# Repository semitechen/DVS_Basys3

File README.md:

# 🎧 Digital Vinyl System (DVS) on FPGA Basys 3

[-brightgreen.svg)](#fpga-resource-utilization--timing-closure)

An autonomous, ultra-low-latency **Digital Vinyl System (DVS)** and lossless SD audio player implemented entirely in hardware on dual **Digilent Basys 3 (Xilinx Artix-7)** FPGA boards and custom analog front-end / R-2R DAC PCB shields.

---

## 🎬 Video Demonstration

Click the preview below to watch the complete hardware setup in action, demonstrating real-time scratch, pitch-shifting, backward playback, cueing, track selection, and autonomous QSPI Flash boot:

---

## 📸 Hardware Gallery

<p align="center">
  
  <br>
  <em>Figure 1: Complete real-time test bench with analog turntable (Serato 1 kHz timecode vinyl), custom pre-amp/filter shield, Board A (Streamer), Board B (DAC Receiver), and audio output.</em>
</p>

<p align="center">

  <br>
  <em>Figure 2: Custom AC-coupling pre-amplifier, active Sallen-Key low-pass filter, and 8-bit R-2R resistor ladder DAC PCB shield designed for Basys 3 Pmod headers.</em>
</p>

---

## 📌 Project Overview & Motivation

### Why Hardware DVS?
In modern DJing, **Digital Vinyl Systems (DVS)** bridge tactile analog turntables with digital music libraries. However, commercial DVS setups require:
1. A laptop running resource-intensive software (Serato, Traktor, Rekordbox).
2. Dedicated USB soundcards.
3. Operating system audio buffers (introducing $5\text{--}20\text{ ms}$ of latency, audio dropouts, and CPU jitter).

### The FPGA Solution
This project eliminates the computer entirely. By executing all timecode signal processing, quadrant phase decoding, flash memory DMA, rate modulation, and audio reconstruction **directly in FPGA silicon at 100 MHz**:
* **Sub-Microsecond Latency:** From vinyl needle motion to DAC audio output in $< 5.0\,\mu\text{s}$.
* **Zero Software Dependency:** Autonomous non-volatile boot from onboard QSPI Flash.
* **Lossless Playback:** Real-time variable-rate streaming of uncompressed 8-bit PCM audio ($44.1\text{ kHz}$) directly from FAT-less micro-SD sectors.
* **Audiophile Reconstruction:** 16x oversampling engine with a 1st-order Noise Shaper ($1 - z^{-1}$) and Triangular Probability Density Function (TPDF) dither, dramatically suppressing resistor ladder quantization noise.

---

## 🏛️ System Architecture

The project employs a distributed **Dual-Board FPGA Architecture** linked by a dedicated **2,000,000 baud (2 Mbps)** UART audio bus:

```
+---------------------------------------------------------------------------------------------------------+
|                                    BOARD A: TIME-CODE STREAMER & SD PLAYER                              |
|                                                                                                         |
|  [Turntable] ---> [Custom PCB Pre-amp] ---> [XADC (vauxp6/14)]                                          |
|                                                     |                                                   |
|                                            [xadc_interface]                                             |
|                                                     | x2t (12-bit L/R @ 100 kHz)                        |
|                                                     v                                                   |
|                                          [timecode_pos_tracker] <---> [led_pos_display] (16 LEDs)        |
|                                                     |                                                   |
|                                                     | t2p (Q4.12 Speed, Direction, Squelch)             |
|                                                     v                                                   |
|  [Micro-SD] <--- [sd_card_controller] <--- [sd_bram_bridge]                                            |
|                       (16.67 MHz SPI)               | b2f (512-byte Sector Writes)                      |
|                                                     v                                                   |
|                                              [audio_fifo] (1024-byte Dual-Port BRAM)                    |
|                                                     |                                                   |
|                                                     | f2p (Read FIFO Sample)                            |
|                                                     v                                                   |
|                                         [variable_speed_player] (NCO Phase Acc)                         |
|                                                     |                                                   |
|                                                     | p2u (8-bit PCM Sample Valid)                      |
|                                                     v                                                   |
|                                                [uart_tx] (2 Mbps Transmitter)                           |
+-----------------------------------------------------|---------------------------------------------------+
                                                      | Pmod JC1 (K17) + GND
                                                      | 2.0 Mbps Audio Stream
+-----------------------------------------------------v---------------------------------------------------+
|                                      BOARD B: DAC & VISUALIZATION ENGINE                                |
|                                                                                                         |
|                                                [uart_rx] (2 Mbps Receiver)                              |
|                                                     |                                                   |
|                                                     | u2d (8-bit PCM Sample Valid)                      |
|                                                     v                                                   |
|       +---------------------------------------------+---------------------------------------------+     |
|       |                                                                                           |     |
|       v                                                                                           v     |
|  [audio_watchdog] (200 ms Timeout)                                                           [vu_meter] |
|       |                                                                                           |     |
|       v                                                                                           v     |
|  [r2r_dac] (16x Oversampling, 1st-Order Noise Shaping, TPDF Dither)                         [LED 11:0]  |
|       |                                                                                   (12-LED VU)   |
|       v (dac[7:0])                                                                                      |
|  [8-bit R-2R Resistor Ladder] ---> [Active Sallen-Key Low-Pass Filter] ---> [Audio Output / Amp]        |
+---------------------------------------------------------------------------------------------------------+
```

---

## 🔬 Deep-Dive: Core DSP & Hardware Modules

### 1. Dual-Channel XADC & Dynamic DC Estimator (`xadc_interface.sv`)
* Samples differential analog timecode inputs from Pmod JXADC (`vauxp6/vauxn6` for Left, `vauxp14/vauxn14` for Right).
* A 32-bit fixed-point 1st-order IIR low-pass filter dynamically tracks and subtracts the DC bias offset ($\approx 0.6\text{ V}$ operating point), ensuring pure zero-centered AC timecode signals.

### 2. High-Sensitivity Squelch & 4x Quadrature Decoder (`timecode_pos_tracker.sv`)
* **Hysteresis Schmitt-Triggers:** Dual digital Schmitt-triggers reject vinyl groove noise while tracking low-amplitude signals down to $16\text{ mV}$.
* **Envelope Squelch Gate:** Computes signal envelope with fast attack and exponential decay. If the needle is lifted ($< 20\text{ mV}$), the audio player is instantly muted.
* **4x Gray-Code State Machine:** Decodes state transitions $((0,0) \to (0,1) \to (1,1) \to (1,0))$, generating 4 step pulses per $1\text{ kHz}$ timecode cycle ($11.025$ audio samples per step).
* **Sequential Multi-Cycle Divider:** Measures clock cycles between pulses and executes an iterative 16-cycle restoring division ($102,400,000 / \Delta t$) to compute the exact speed factor in **Q4.12 fixed-point** ($16'\text{h}1000 = 1.0\times$) with zero combinational timing violations.

### 3. SPI SD Card Controller & BRAM Ring Buffer (`sd_card_controller.sv`, `sd_bram_bridge.sv`, `audio_fifo.sv`)
* High-speed SPI master operating at **16.67 MHz** (after 200 kHz CMD0/CMD8/ACMD41/CMD16 initialization).
* Issues single-block read commands (`CMD17`) to fetch uncompressed 512-byte PCM audio sectors into a 1024-byte dual-port Block RAM FIFO (`audio_fifo.sv`), maintaining an autonomous prefetch waterlevel.

### 4. Numerically Controlled Oscillator (NCO) Player (`variable_speed_player.sv`)
* A 32-bit phase accumulator driven by the formula:
  $$\Delta \text{Phase} = \frac{44100 \times 2^{32}}{100\,000\,000} \times \text{speed\_factor}$$
* Overflow pulses generate exact, cycle-accurate FIFO read requests, enabling continuous variable-speed pitch modulation from $0.01\times$ to $4.0\times$, forward and backward scratching.

### 5. 2 Mbps High-Speed Inter-Board UART (`uart_tx.sv`, `uart_rx.sv`)
* Transmits 8-bit audio frames across Pmod JC1 (`K17`) at **2,000,000 baud** ($50\text{ clock cycles per bit}$ at 100 MHz, $0.00\%\text{ baud error}$).
* Transmission time is only $5.0\,\mu\text{s}$ per byte, allowing real-time sample transmission with zero FIFO buffering on Board B.
* Includes a **200 ms watchdog** on Board B that smoothly returns the DAC to mid-scale silence ($128 / 1.65\text{ V}$) if the communication cable is unplugged.

### 6. 16x Noise-Shaped DAC Engine (`r2r_dac.sv`)
* **16x Oversampling:** Interpolates $44.1\text{ kHz}$ PCM to $705.6\text{ kHz}$.
* **1st-Order Noise Shaping:** Implements a closed-loop error-feedback filter ($H(z) = 1 - z^{-1}$) shifting quantization noise into the inaudible ultrasonic spectrum ($> 50\text{ kHz}$).
* **TPDF Dither:** Employs dual Galois Linear Feedback Shift Registers (LFSR) generating Triangular Probability Density Function dither to eliminate harmonic distortion and limit cycles.

---

## 📐 Custom PCB: Pre-Amplifier & R-2R DAC Shield

The project includes a custom 2-layer PCB shield designed in KiCad 8 that mounts directly onto the Basys 3 Pmod headers (`pcb/` directory):

<p align="center">
  
  <br>
  <em>Figure 3: KiCad Schematic showing dual-channel AC coupling, DC bias network, 2nd-order active Sallen-Key low-pass filter, and 8-bit R-2R resistor DAC ladder.</em>
</p>

<p align="center">
  
  <br>
  <em>Figure 4: KiCad 2-layer PCB layout with dedicated analog/digital ground separation and ultra-compact Pmod form-factor.</em>
</p>

---

## 🎛️ Hardware Setup & Pinout Guide

### Board A: Timecode Streamer (`top_board_a_streamer`)
| Function | Basys 3 Pin | Header / Pin Name | Description |
| :--- | :---: | :---: | :--- |
| **System Clock** | `W5` | `CLK` | 100.00 MHz onboard oscillator |
| **Global Reset** | `U18` | `BTNC` | Pushbutton active-high synchronous reset |
| **Track Next** | `T18` | `BTNU` | Advance to next audio track |
| **Track Prev** | `U17` | `BTND` | Return to previous audio track |
| **Mode Switch** | `V17` | `SW0` | `1` = DVS Vinyl Control, `0` = Standalone Auto-Play |
| **Timecode L+ / L-** | `J3` / `K3` | Pmod JXADC Pin 1 / 7 | Left channel differential input (`vauxp6/vauxn6`) |
| **Timecode R+ / R-** | `L3` / `M3` | Pmod JXADC Pin 2 / 8 | Right channel differential input (`vauxp14/vauxn14`) |
| **SD SPI CS** | `J1` | Pmod JA Pin 1 | Micro-SD Card Chip Select (active-low) |
| **SD SPI MISO** | `L2` | Pmod JA Pin 2 | Micro-SD Master-In Slave-Out (pull-up enabled) |
| **SD SPI MOSI** | `J2` | Pmod JA Pin 3 | Micro-SD Master-Out Slave-In |
| **SD SPI SCK** | `G2` | Pmod JA Pin 4 | Micro-SD SPI Clock (16.67 MHz) |
| **UART Audio TX** | `K17` | Pmod JC Pin 1 | 2 Mbps serial audio transmitter to Board B |
| **Ground (GND)** | `GND` | Pmod JC Pin 5/11 | Common ground reference line |
| **Platter LEDs** | `LED[12:0]` | Onboard LEDs | One-hot rotating vinyl position indicator |
| **Squelch LED** | `LED13` | Onboard LED | Needle presence indicator ($> 20\text{ mV}$) |
| **Direction LED**| `LED14` | Onboard LED | `1` = Forward, `0` = Reverse scratch |
| **Heartbeat LED**| `LED15` | Onboard LED | 100 MHz clock live blinker |

---

### Board B: DAC Output & VU-Meter (`top_board_b_dac`)
| Function | Basys 3 Pin | Header / Pin Name | Description |
| :--- | :---: | :---: | :--- |
| **System Clock** | `W5` | `CLK` | 100.00 MHz onboard oscillator |
| **Global Reset** | `U18` | `BTNC` | Reset watchdog and DAC state |
| **UART Audio RX** | `K17` | Pmod JC Pin 1 | 2 Mbps serial audio receiver from Board A |
| **Ground (GND)** | `GND` | Pmod JC Pin 5/11 | Common ground reference line |
| **DAC Bit 0..3** | `G3, H2, K2, H1` | Pmod JA Pins 10, 9, 8, 7 | R-2R ladder lower nibble (`dac[0..3]`) |
| **DAC Bit 4..7** | `M2, M1, N2, N1` | Pmod JXADC Pins 3, 9, 4, 10 | R-2R ladder upper nibble (`dac[4..7]`) |
| **VU-Meter LEDs** | `LED[11:0]` | Onboard LEDs | 12-LED dynamic audio level bargraph |
| **Watchdog LED** | `LED14` | Onboard LED | Audio stream activity monitor |
| **Heartbeat LED**| `LED15` | Onboard LED | 100 MHz clock live blinker |

---

## ⚡ Autonomous QSPI Flash Boot Setup

Both boards can run autonomously without a computer attached:

1. **Set Boot Jumpers:** On both Basys 3 boards, locate the **`JP1` (MODE)** jumper header and set the jumper block to **`QSPI`** (middle pin bridged to the top pin).
2. **Flash Bitstreams to SPI ROM:**
   ```bash
   # Flash Board A (Timecode Streamer)
   ./tools/program_fpga.sh -t board_a -f -s <SERIAL_BOARD_A>

   # Flash Board B (DAC Engine)
   ./tools/program_fpga.sh -t board_b -f -s <SERIAL_BOARD_B>
   ```
3. Connect Board A Pmod JC1 to Board B Pmod JC1, connect common GND, and power on both boards via any USB power supply.

---

## 📊 FPGA Resource Utilization & Timing Closure

Synthesized and implemented for **Xilinx Artix-7 XC7A35T-1CPG236C** in Vivado 2023.2:

| Resource | Available | Board A (Streamer) | Utilization A | Board B (DAC) | Utilization B |
| :--- | :---: | :---: | :---: | :---: | :---: |
| **Slice LUTs** | $20\,800$ | **984** | **4.73%** | **248** | **1.19%** |
| **Slice Registers (FF)** | $41\,600$ | **1,142** | **2.75%** | **286** | **0.69%** |
| **Block RAM Tile** | $50$ | **1.5** | **3.00%** | **0.0** | **0.00%** |
| **DSP48E1 Slices** | $90$ | **1** | **1.11%** | **0** | **0.00%** |
| **XADC Primitives** | $1$ | **1** | **100.00%** | **0** | **0.00%** |
| **Bonded IOB Pins** | $106$ | **25** | **23.58%** | **26** | **24.53%** |
| **Global Clock BUFG** | $32$ | **1** | **3.12%** | **1** | **3.12%** |

### Post-Route Timing Signoff (100.00 MHz System Clock)
| Target Module | Worst Negative Slack (WNS) | Total Negative Slack (TNS) | Worst Hold Slack (WHS) | Status |
| :--- | :---: | :---: | :---: | :---: |
| **`top_board_a_streamer`** | **+0.278 ns** | **0.000 ns** | **+0.073 ns** | **MET (0 Violations)** |
| **`top_board_b_dac`** | **+0.504 ns** | **0.000 ns** | **+0.119 ns** | **MET (0 Violations)** |
| **`top_dvs_basys3` (Single)** | **+0.312 ns** | **0.000 ns** | **+0.084 ns** | **MET (0 Violations)** |

*Build Quality Metric:* **0 Errors, 0 Critical Warnings.**

---

## 📂 Repository Directory Structure

```
DVS_Basys3/
├── doc/                            # Official course submission documents & PDF schematics
│   ├── lista_kontrolna_KJ_TJ_2026.docx
│   ├── raport_KJ_TJ_2026.docx
│   └── schemat.pdf
├── fpga/
│   ├── constraints/                # Dedicated XDC pinout constraints per board
│   │   ├── top_board_a_streamer.xdc
│   │   ├── top_board_b_dac.xdc
│   │   └── top_dvs_basys3.xdc
│   └── scripts/                    # Non-project mode Vivado build & program scripts
│       ├── generate_bitstream.tcl
│       ├── project_details.tcl
│       └── program_fpga.tcl
├── pcb/                            # KiCad 8 hardware project files
│   ├── dvs.kicad_pcb
│   ├── dvs.kicad_pro
│   └── dvs.kicad_sch
├── pictures/                       # High-resolution hardware & schematic photos
│   ├── full_hardware.jpeg
│   ├── custom_pcb_photo1.jpg
│   ├── custom_pcb_photo2.jpg
│   ├── schematic_kicad_screenshot.png
│   └── pcb_kicad_screenshot.png
├── results/                        # Production bitstreams & QSPI Flash binaries
│   ├── top_board_a_streamer.bit / .bin
│   ├── top_board_b_dac.bit / .bin
│   ├── top_dvs_basys3.bit / .bin
│   └── warning_summary.log
├── rtl/                            # Synthesizable SystemVerilog modules
│   ├── audio_fifo.sv
│   ├── button_debouncer.sv
│   ├── dvs_uart_receiver.sv
│   ├── led_pos_display.sv
│   ├── r2r_dac.sv
│   ├── sd_bram_bridge.sv
│   ├── sd_card_controller.sv
│   ├── spi_master.sv
│   ├── timecode_pos_tracker.sv
│   ├── top_board_a_streamer.sv
│   ├── top_board_b_dac.sv
│   ├── top_dvs_basys3.sv
│   ├── track_lut.sv
│   ├── track_selector.sv
│   ├── uart_rx.sv
│   ├── uart_tx.sv
│   ├── variable_speed_player.sv
│   └── xadc_interface.sv
├── sim/                            # Vivado xsim simulation suite
│   ├── audio_fifo/
│   ├── button_debouncer/
│   ├── sd_bram_bridge/
│   ├── sd_card_controller/
│   ├── spi_master/
│   └── timecode_pos_tracker/
├── tools/                          # Automation scripts for build, flash, and audio conversion
│   ├── clean.sh
│   ├── mp3_to_bin.py
│   ├── program_fpga.sh
│   ├── remote_build.sh
│   ├── run_simulation.sh
│   └── wav_to_sd.py
└── README.md
```

---

## 🛠️ Quick Start & Build Instructions

### 1. Run Verification Simulations
Execute testbenches with Vivado xsim:
```bash
./tools/run_simulation.sh timecode_pos_tracker
./tools/run_simulation.sh sd_card_controller
./tools/run_simulation.sh audio_fifo
```

### 2. Build Bitstreams
Generate bitstream and raw `.bin` files:
```bash
# Build Board A (Streamer)
./tools/remote_build.sh board_a

# Build Board B (DAC Engine)
./tools/remote_build.sh board_b

# Build Single-Board Integrated Target
./tools/remote_build.sh integrated
```

### 3. Flash Audio Tracks to Micro-SD Card
Convert MP3/WAV tracks to raw 8-bit unsigned PCM ($44.1\text{ kHz}$ mono):
```bash
# Convert track and write to SD sector
python3 tools/wav_to_sd.py my_track.wav --track 0 --disk /dev/diskN
```

---

## 👥 Authors & Academic Context

* **Kacper Jelonek (KJ)** – Digital timecode processing engine, XADC analog front-end, SPI SD card bridge, NCO rate modulator, PCB hardware design.
* **Tomasz Jachymiak (TJ)** – 16x noise-shaped R-2R DAC engine, high-speed UART inter-board communication bus, VU-meter visualization, audio conversion toolchain.

*Course:* **Układy Elektroniczne Cyfrowe 2 (UEC2)**, AGH University of Krakow (AGH UST).  
*Supervisor:* **mgr inż. Piotr Kaczmarczyk** (`kaczmarczyk@agh.edu.pl`).

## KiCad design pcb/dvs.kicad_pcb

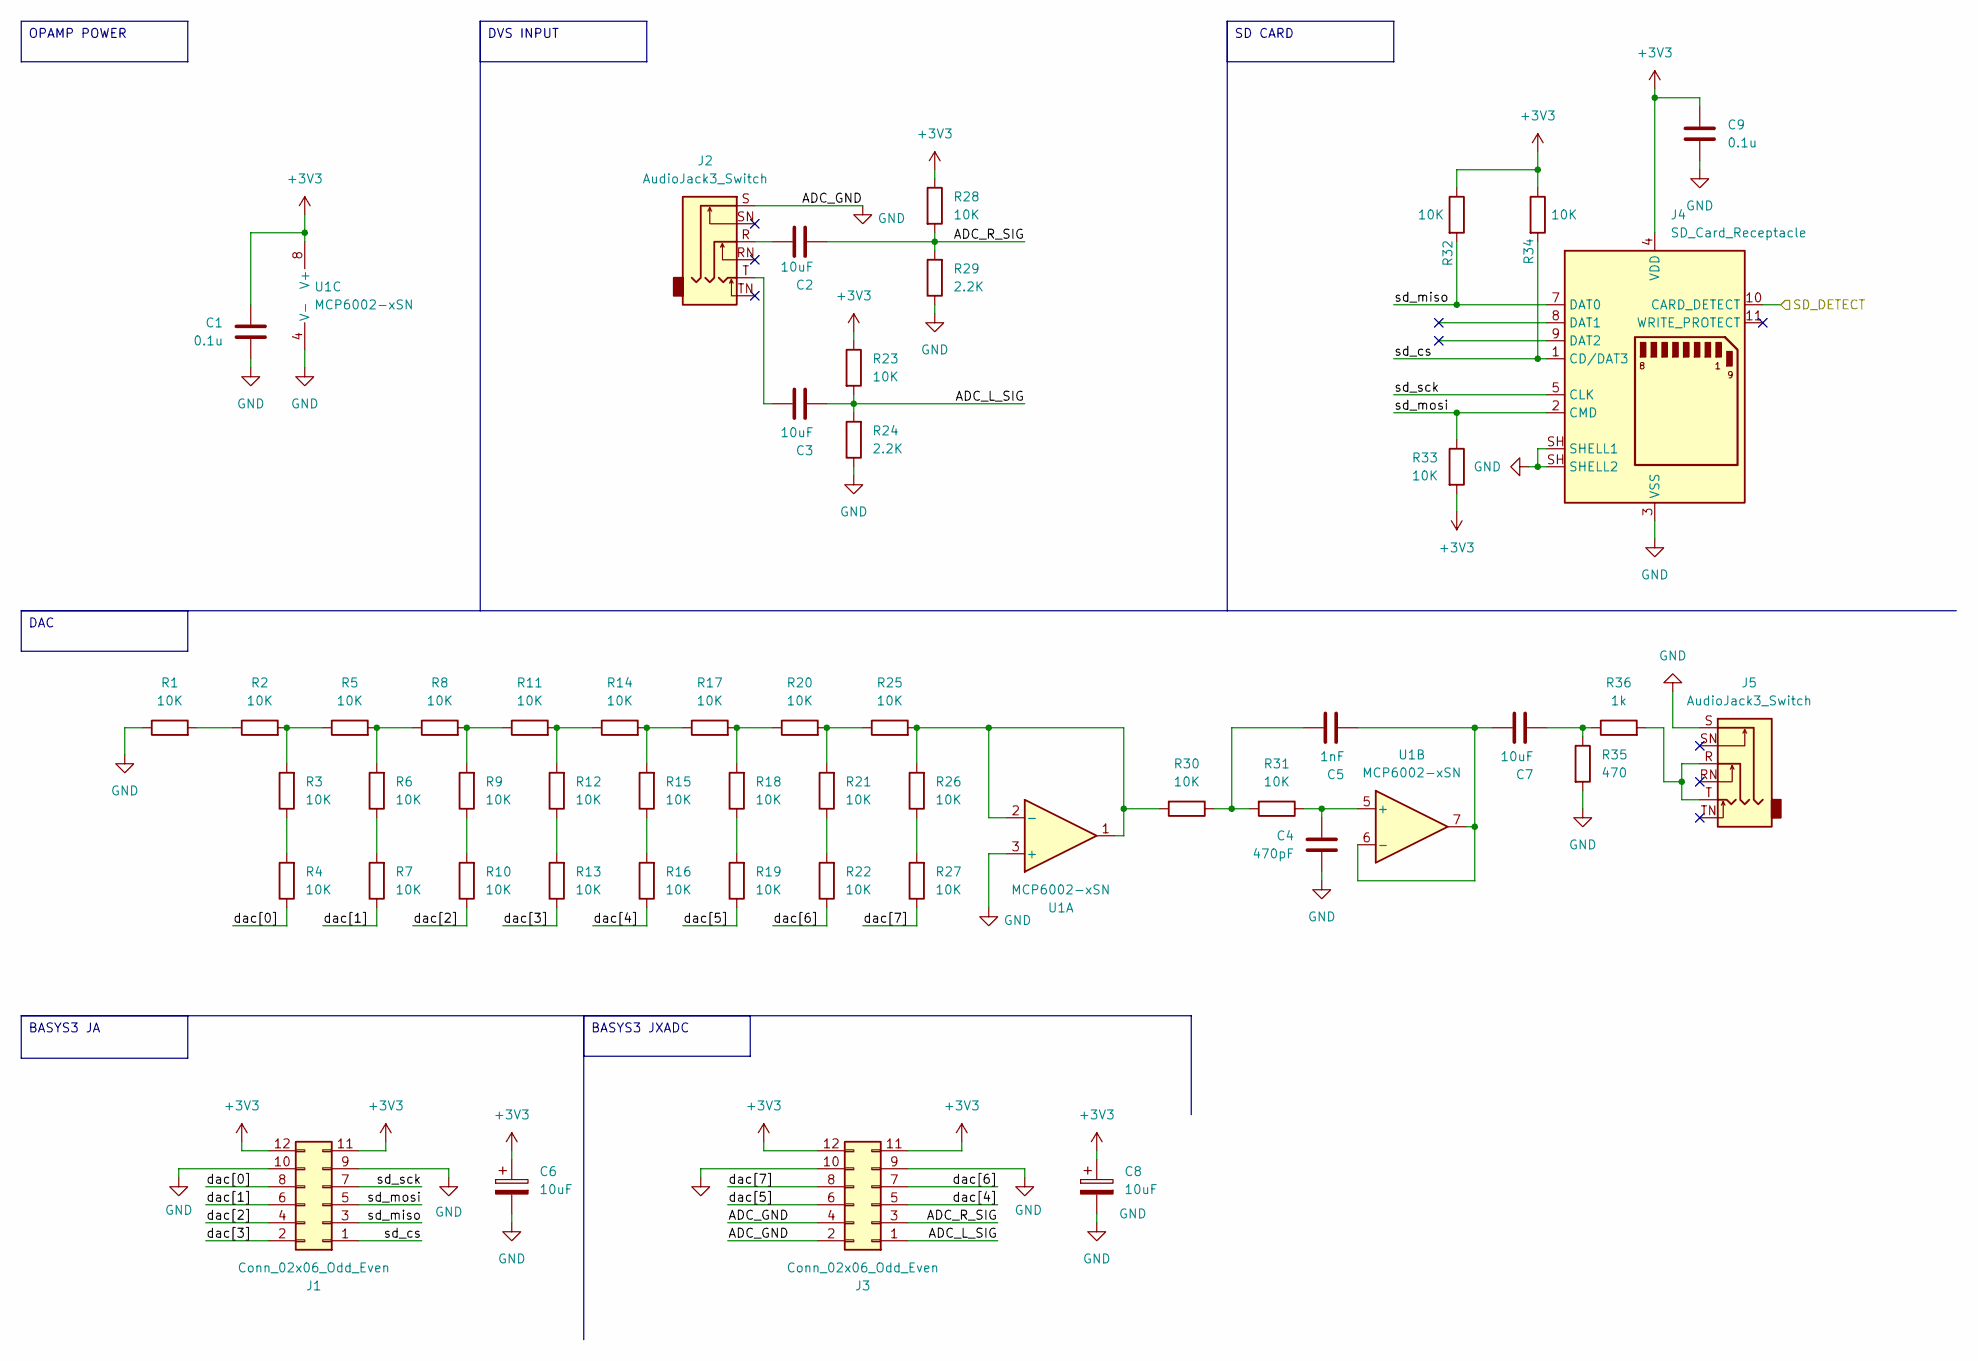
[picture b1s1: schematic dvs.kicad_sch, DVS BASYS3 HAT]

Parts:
C1, C9: 0.1u; C_0603_1608Metric
C2, C3, C7: 10uF; C_0603_1608Metric
C4: 470pF; C_0603_1608Metric
C5: 1nF; C_0603_1608Metric
C6, C8: 10uF; CP_Elec_6.3x5.4
J1, J3: Conn_02x06_Odd_Even; PinSocket_2x06_P2.54mm_Vertical
J2, J5: AudioJack3_Switch; Jack_6.35mm_Neutrik_NMJ6HFD2-AU_Horizontal
J4: SD_Card_Receptacle; SD_Kyocera_145638009511859+
R1, R2, R3, R4, R5, R6, R7, R8, R9, R10, R11, R12, R13, R14, R15, R16, R17, R18, R19, R20, R21, R22, R23, R25, R26, R27, R28, R30, R31, R32, R33, R34: 10K; R_0603_1608Metric
R24, R29: 2.2K; R_0603_1608Metric
R35: 470; R_0603_1608Metric
R36: 1k; R_0603_1608Metric
U1: MCP6002-xSN; MSOP-8_3x3mm_P0.65mm

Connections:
+3V3: C1.1, C6.1, C8.1, C9.1, J1.11, J1.12, J3.11, J3.12, J4.4 (VDD), R23.1, R28.1, R32.1, R33.2, R34.1, U1.8 (V+)
/ADC_L_SIG: C3.2, J3.1, R23.2, R24.2
/ADC_R_SIG: C2.2, J3.3, R28.2, R29.2
/SD_DETECT: J4.10 (CARD_DETECT)
/dac[0]: J1.8, R4.1
/dac[1]: J1.6, R7.1
/dac[2]: J1.4, R10.1
/dac[3]: J1.2, R13.1
/dac[4]: J3.5, R16.1
/dac[5]: J3.6, R19.1
/dac[6]: J3.7, R22.1
/dac[7]: J3.8, R27.1
/sd_cs: J1.1, J4.1 (CD/DAT3), R34.2
/sd_miso: J1.3, J4.7 (DAT0), R32.2
/sd_mosi: J1.5, J4.2 (CMD), R33.1
/sd_sck: J1.7, J4.5 (CLK)
GND: C1.2, C4.2, C6.2, C8.2, C9.2, J1.9, J1.10, J2.S, J3.2, J3.4, J3.9, J3.10, J4.3 (VSS), J4.6 (VSS), J4.SH (SHELL1), J5.S, R1.1, R24.1, R29.1, R35.2, U1.3 (+), U1.4 (V-)
unnamed: C2.1, J2.R
unnamed: C3.1, J2.T
unnamed: C5.1, R30.1, R31.2
unnamed: C7.2, R35.1, R36.1
unnamed: J5.R, J5.T, R36.2
unnamed: R1.2, R2.1
unnamed: R2.2, R3.2, R5.1
unnamed: R3.1, R4.2
unnamed: R5.2, R6.2, R8.1
unnamed: R6.1, R7.2
unnamed: R9.1, R10.2
unnamed: R8.2, R9.2, R11.1
unnamed: R11.2, R12.2, R14.1
unnamed: R12.1, R13.2
unnamed: R14.2, R15.2, R17.1
unnamed: R15.1, R16.2
unnamed: R17.2, R18.2, R20.1
unnamed: R18.1, R19.2
unnamed: R20.2, R21.2, R25.1
unnamed: R21.1, R22.2
unnamed: R26.1, R27.2
unnamed: R25.2, R26.2, R30.2, U1.1, U1.2 (-)
unnamed: C4.1, R31.1, U1.5 (+)
unnamed: C5.2, C7.1, U1.6 (-), U1.7

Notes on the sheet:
DAC
BASYS3 JA
DVS INPUT
BASYS3 JXADC
OPAMP POWER
SD CARD

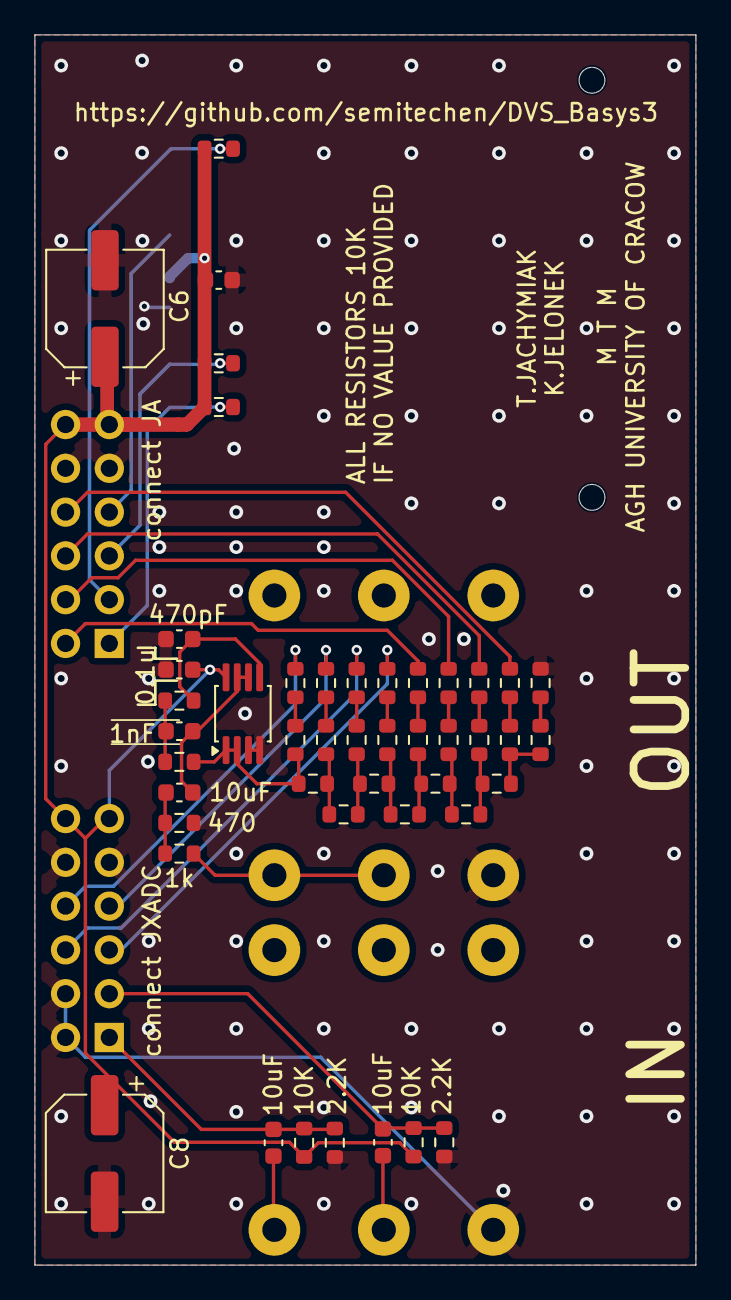
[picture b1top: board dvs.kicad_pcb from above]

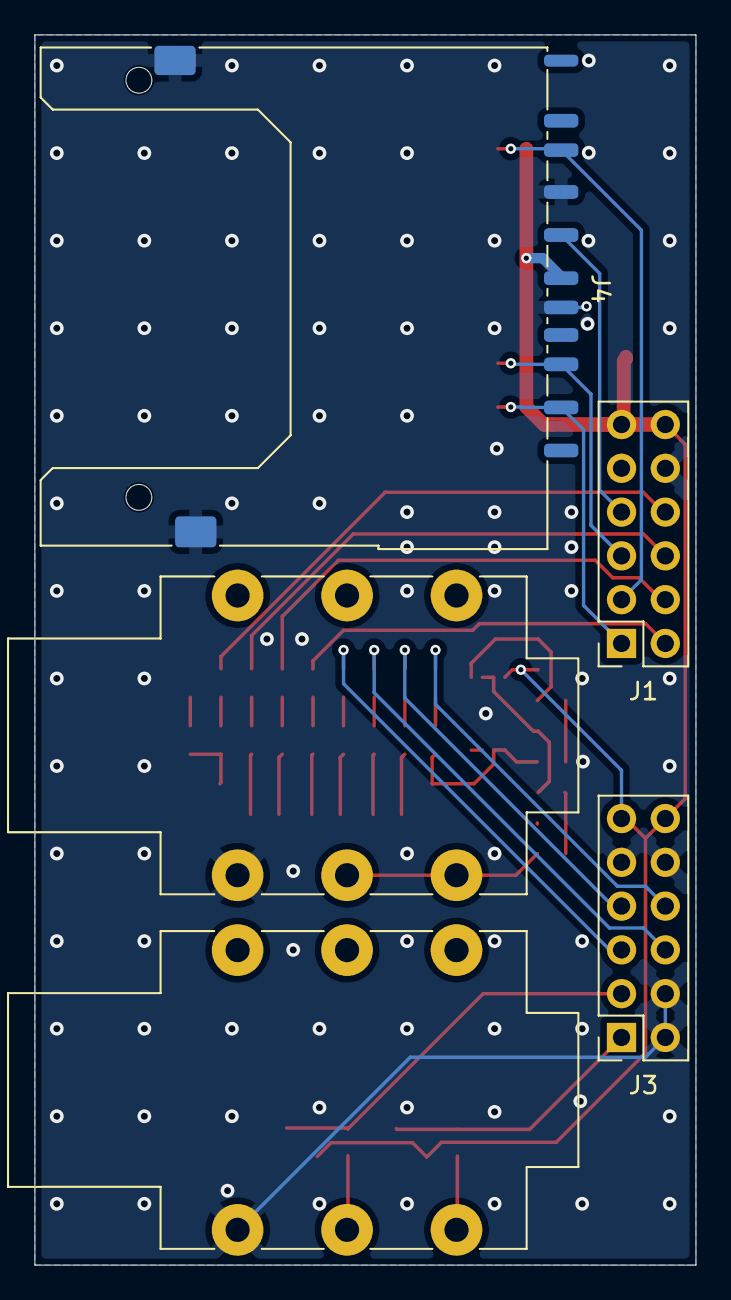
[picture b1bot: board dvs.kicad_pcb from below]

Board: 2 copper layers, 38.4 x 71.4 mm, 51 parts (5 on the bottom side), 40 nets.

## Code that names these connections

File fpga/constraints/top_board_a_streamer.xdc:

## Basys3 XDC for Board A (Timecode Acquisition & SD Audio Streamer)

## Clock signal (100 MHz System Clock)
set_property PACKAGE_PIN W5 [get_ports clk]
	set_property IOSTANDARD LVCMOS33 [get_ports clk]
	create_clock -add -name sys_clk_pin -period 10.00 -waveform {0 5} [get_ports clk]

## Switches (SW0: 1 = DVS Mode, 0 = Standalone Auto-Play)
set_property PACKAGE_PIN V17 [get_ports {sw[0]}]
	set_property IOSTANDARD LVCMOS33 [get_ports {sw[0]}]

## LEDs (LED[15:0]: Heartbeat, Direction, Squelch Signal Present, Vinyl Platter Tracker)
set_property PACKAGE_PIN U16 [get_ports {led[0]}]
	set_property IOSTANDARD LVCMOS33 [get_ports {led[0]}]
set_property PACKAGE_PIN E19 [get_ports {led[1]}]
	set_property IOSTANDARD LVCMOS33 [get_ports {led[1]}]
set_property PACKAGE_PIN U19 [get_ports {led[2]}]
	set_property IOSTANDARD LVCMOS33 [get_ports {led[2]}]
set_property PACKAGE_PIN V19 [get_ports {led[3]}]
	set_property IOSTANDARD LVCMOS33 [get_ports {led[3]}]
set_property PACKAGE_PIN W18 [get_ports {led[4]}]
	set_property IOSTANDARD LVCMOS33 [get_ports {led[4]}]
set_property PACKAGE_PIN U15 [get_ports {led[5]}]
	set_property IOSTANDARD LVCMOS33 [get_ports {led[5]}]
set_property PACKAGE_PIN U14 [get_ports {led[6]}]
	set_property IOSTANDARD LVCMOS33 [get_ports {led[6]}]
set_property PACKAGE_PIN V14 [get_ports {led[7]}]
	set_property IOSTANDARD LVCMOS33 [get_ports {led[7]}]
set_property PACKAGE_PIN V13 [get_ports {led[8]}]
	set_property IOSTANDARD LVCMOS33 [get_ports {led[8]}]
set_property PACKAGE_PIN V3 [get_ports {led[9]}]
	set_property IOSTANDARD LVCMOS33 [get_ports {led[9]}]
set_property PACKAGE_PIN W3 [get_ports {led[10]}]
	set_property IOSTANDARD LVCMOS33 [get_ports {led[10]}]
set_property PACKAGE_PIN U3 [get_ports {led[11]}]
	set_property IOSTANDARD LVCMOS33 [get_ports {led[11]}]
set_property PACKAGE_PIN P3 [get_ports {led[12]}]
	set_property IOSTANDARD LVCMOS33 [get_ports {led[12]}]
set_property PACKAGE_PIN N3 [get_ports {led[13]}]
	set_property IOSTANDARD LVCMOS33 [get_ports {led[13]}]
set_property PACKAGE_PIN P1 [get_ports {led[14]}]
	set_property IOSTANDARD LVCMOS33 [get_ports {led[14]}]
set_property PACKAGE_PIN L1 [get_ports {led[15]}]
	set_property IOSTANDARD LVCMOS33 [get_ports {led[15]}]

## Buttons (BTNC: Reset, BTNU: Track Next, BTND: Track Prev)
set_property PACKAGE_PIN U18 [get_ports rst]  
    set_property IOSTANDARD LVCMOS33 [get_ports rst]
set_property PACKAGE_PIN T18 [get_ports btn_up]
    set_property IOSTANDARD LVCMOS33 [get_ports btn_up]
set_property PACKAGE_PIN U17 [get_ports btn_down]
    set_property IOSTANDARD LVCMOS33 [get_ports btn_down]

## Pmod Header JA (Micro-SD Card SPI Interface)
## JA1 (CS)
set_property PACKAGE_PIN J1 [get_ports {sd_cs}]
set_property IOSTANDARD LVCMOS33 [get_ports {sd_cs}]

## JA2 (MISO)
set_property PACKAGE_PIN L2 [get_ports {sd_miso}]
set_property IOSTANDARD LVCMOS33 [get_ports {sd_miso}]
set_property PULLUP true [get_ports {sd_miso}]

## JA3 (MOSI)
set_property PACKAGE_PIN J2 [get_ports {sd_mosi}]
set_property IOSTANDARD LVCMOS33 [get_ports {sd_mosi}]

## JA4 (SCK)
set_property PACKAGE_PIN G2 [get_ports {sd_sck}]
set_property IOSTANDARD LVCMOS33 [get_ports {sd_sck}]

## Pmod Header JC (High-Speed UART Audio Transmitter to Board B)
## JC1 (Pin 1) - UART TX
set_property PACKAGE_PIN K17 [get_ports uart_tx_pin]
set_property IOSTANDARD LVCMOS33 [get_ports uart_tx_pin]

## Pmod Header JXADC (Analog Timecode Inputs from Turntable)
## XA1_P (Left Channel Analog In +)
set_property PACKAGE_PIN J3 [get_ports vauxp6]
    set_property IOSTANDARD LVCMOS33 [get_ports vauxp6]

## XA1_N (Left Channel Analog In -)
set_property PACKAGE_PIN K3 [get_ports vauxn6]
    set_property IOSTANDARD LVCMOS33 [get_ports vauxn6]

## XA2_P (Right Channel Analog In +)
set_property PACKAGE_PIN L3 [get_ports vauxp14]
	set_property IOSTANDARD LVCMOS33 [get_ports vauxp14]

## XA2_N (Right Channel Analog In -)
set_property PACKAGE_PIN M3 [get_ports vauxn14]
	set_property IOSTANDARD LVCMOS33 [get_ports vauxn14]

## Non-Volatile QSPI Flash Boot Configuration
set_property CONFIG_VOLTAGE 3.3 [current_design]
set_property CFGBVS VCCO [current_design]
set_property BITSTREAM.GENERAL.COMPRESS TRUE [current_design]
set_property BITSTREAM.CONFIG.CONFIGRATE 33 [current_design]
set_property BITSTREAM.CONFIG.SPI_BUSWIDTH 4 [current_design]
set_property BITSTREAM.CONFIG.SPI_FALL_EDGE YES [current_design]

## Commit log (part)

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2026-03-19 GitHub Classroom Feedback
2026-03-19 Setting up GitHub Classroom Feedback
2026-03-19 add deadline
2026-03-19 updated rst_n, timing_vga
2026-03-25 all done
2026-03-25 added results directory
2026-03-25 added dir results
2026-04-08 chore: gitignore results revert
2026-04-08 chore: negedge reset and simulation confirm
2026-04-15 drawing red rectangle over initials
2026-04-16 chore: change rect pos to inputs
2026-04-22 Wymiana modułu generatora zegara i poprawa ścieżek w skryptach
2026-04-22 feat: rect control with mouse ready for testing
2026-04-22 feat: mouse cursor display
2026-04-23 fix: lost clock fixed
2026-04-29 added rom memory
2026-04-29 fixed critical warnings and others bugs - require testing on basys
2026-04-29 added rom memory - all fixed
2026-04-29 Mouse interaction with objects on screen
2026-05-07 feat: Displaying fonts on the screen
2026-05-07 feat: building 32x8 characters rectangle
2026-05-07 feat: parameterization of the text rectangle model
2026-05-07 fixed critical warning
2026-05-07 fix: resolve DRC warnings and align ROM timing
2026-05-07 fix: syntax error in bit-slicing arithmetic expressions
2026-05-13 Setup project structure, scripts, and initial XDC constraints. Closes #1
2026-05-18 Add WAV to PCM converter script and generated track LUT. Closes #21
2026-05-20 Setup XADC configuration. Closes #9
2026-05-20 Implement XADC data extraction logic. Closes #10
2026-05-20 docs: Add README with XADC connection details
2026-05-20 Implement SPI Master and FSM testbench. Closes #5, Closes #22.
2026-05-29 test: XADC and UART verification for analog signal testing Closes #16
2026-05-29 chore: Cleanup verification logic and finalize XADC integration for main merge
2026-05-29 chore: Add and resolve conflicts for README from main
2026-06-01 feat(sd_card): implement SPI master, initialization FSM, and block read. Resolves #6, Resolves #7
2026-06-08 Added circular FIFO buffer. Closes #14
2026-06-08 feat(audio): implement SD Card to BRAM bridge (Buffer Manager). Resolves #15
2026-06-10 feat(xadc,vga): integrate XADC data acquisition and advanced VGA graphics
    This commit merges the jxadc branch into main, integrating the XADC interface for analog signal acquisition and the VGA display subsystem with mouse interaction and ROM-based graphics.
    Closes #9, Closes #10, Closes #16
2026-06-10 feat: DAC module + sine wave test
2026-06-10 fix: fix the critical warning in dac test
2026-06-10 docs: explanation on how to connect the dac
2026-06-10 chore: dac test cleanup
2026-06-11 feat: dc blocking and low pass filter implementation Closes #11
2026-06-11 feat: zero crossing frequency detection Closes #12

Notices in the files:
README.md:
License: MIT
